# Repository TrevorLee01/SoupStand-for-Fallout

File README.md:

# Soup-Stand 🎧🦝 // FALLOUT PROJECT
A multifunctional pastel and tanuki (Soup!) themed headphone stand with integrated speaker, storage, and cable organization.

Created by Youna Son & Trevor Lee for Fallout / Hack Club.
✍️(◔◡◔)

ONSHAPE LINK: https://cad.onshape.com/documents/8000dcbb44917720ecbb4f72/w/cf3f842479549c0ffed44f74/e/c42a8c0b9d5092f488456cc3

  BOM INCLUDED IN THE FILES! "BOM.csv" 
or:
https://docs.google.com/spreadsheets/d/1DdpiUlOQK0JWII-2MIieYWEtMwIM88fONbokk5xA5AE/edit?gid=0#gid=0

______________

# What Is A Soup Stand ❓ο(=•ω＜=)ρ⌒☆
A Soup Stand is a hybrid desk accessory designed to combine organization, audio, and aesthetics into a single, cute tanuki.

The project combines:
- A headphone stand
- Speaker
- Compact desk organization
- Decorative accessory

The design was inspired by:
- pastel tech aesthetics (I've always wanted a cute set-up 💔)
- Japanese lifstyle product design (look how Muji designs their aesthetically pleasing stationary!)

+ gaming/anime desk culture:

But now... imagine the Soup Stand in these images

Unlike most headphone stads that are purely functional and even weirdly abstract looking, our product is designed to feel cozy. 

_________________

# Why It Was Made 🛠️ o(*￣▽￣*)o

We noticed that most desk accessories feel:
- boringggggggg
- overly industrial (late-stage capitalism tsk tsk)
- visually disconnected from modern aesthetic setups

At the same time, headphones are left:
- on desks (takes so much space on my limited desk space)
- hanging off monitors
- tangled in wires

So..
We wanted to create something that:
1) organizees a worspace
2) improves desk appearance
3) emotionally engaging rather than purely mechanical

A major goal of this project was combing hardware engineering (the opportunity fallout gives us) with product branding and visual interesting design

__________

# Features ✨   (*^▽^*)
## 🎧 Headphone Stand 
Supports over-ear headphones while keeping them accessible and off and desk surface 
## 🔊 Speaker
Internal space planned for small speaker 

~ plays your favorite song ~
## 🎨Decorative Design 

This structure is designed around 3D printing and prototyping!

________

# How It Works ╰(*°▽°*)╯

The headphones rest of the upper support section of the stand.

The lower body contains:
- eletronic compartment
- structural support (flat base)
- speakers

There are 3 buttons:
TOP: increase volume
MIDDLE: pause music/sound
BOTTOM: decrease volume

All 3 at once is the power on and off button

  !! POTENTIALLY:customizable parts ?? !!
  __________

  # How to build
  ______
  How to Assemble & Use Your Soup Stand
1) Print the Parts: Download the .step files from the repository and 3D print the upper headset support, main body, and base storage compartment.

2) Mount the Electronics: Secure your custom PCB inside the lower electronic compartment. Fit the speaker into its designated internal slot.

3) Route the Cables & Connect: Pass your speaker and power cables through the integrated cable organization channels out to the back of the stand.

4) Final Assembly: Align the upper support section with the main body and snap/screw them together.

5) How to Use: Place the Soup Stand on your desk and plug the power/audio cable into your computer or power source. Rest your over-ear headphones on Soup’s head to keep your desk clutter-free, use the lower tray for compact desk storage, and play your favorite music directly through the integrated speaker!

  # PICTURES!!!
  THIS OUR FINISHED CAD YAYYY (no color because we rendered it with color instead)

  THIS IS OUR PCB rah!!

  extra image of rendering not in the zine (NO FACE) :

# Credits
- Onshape (CAD)
- GitHub (here!)
- Canva (Zine)
- 3D printing
- and obviously... FALLOUT! since our headphone stand is based off the mascot Soup!

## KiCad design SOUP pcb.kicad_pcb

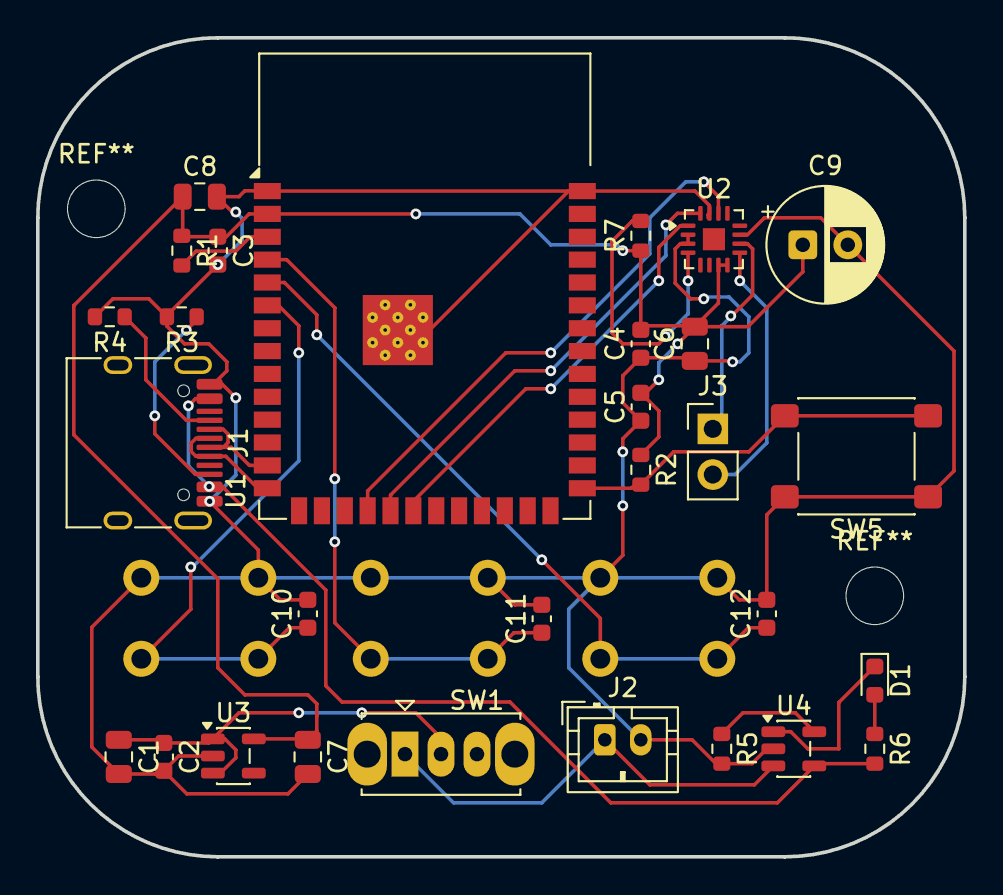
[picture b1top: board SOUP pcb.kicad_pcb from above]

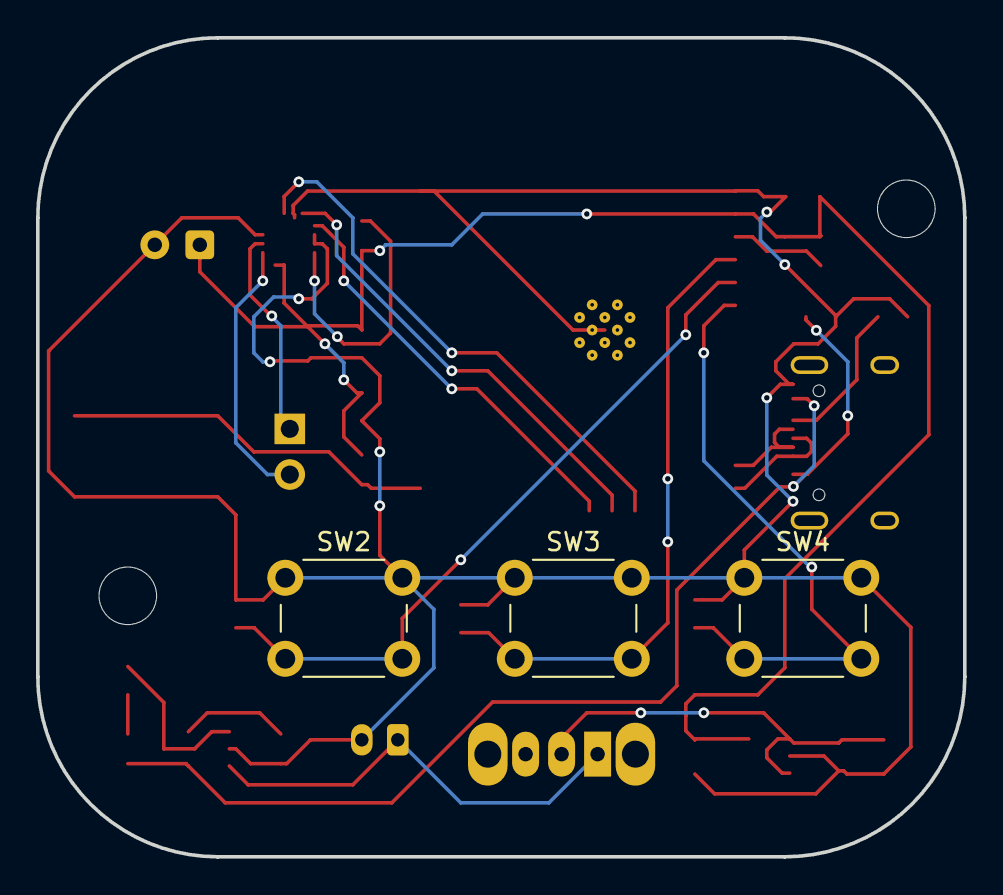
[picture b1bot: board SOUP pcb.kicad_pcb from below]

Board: 2 copper layers, 51.5 x 45.5 mm, 32 parts (3 on the bottom side), 23 nets.

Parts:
C1, C6, C7: 10μf; C_0805_2012Metric
C2, C4, C5, C10, C11, C12: 0.1μf; C_0603_1608Metric
C3: 1μf; C_0603_1608Metric
C8: 10 μf; C_0805_2012Metric
C9: 220μf; CP_Radial_D6.3mm_P2.50mm
D1: LED; LED_0603_1608Metric
J1: USB_C_Receptacle_USB2.0_16P; USB_C_Receptacle_HRO_TYPE-C-31-M-12
J2: Conn_01x02; JST_PH_B2B-PH-K_1x02_P2.00mm_Vertical
J3: Conn_01x02; PinHeader_1x02_P2.54mm_Vertical
R1: 10K; R_0603_1608Metric
R2: 10k; R_0603_1608Metric
R3, R4: 5.1K; R_0603_1608Metric
R5: 2k; R_0603_1608Metric
R6: 330; R_0603_1608Metric
R7: 300k; R_0603_1608Metric
SW1: SW_SPST; SW_Slide_SPDT_Straight_CK_OS102011MS2Q
SW2, SW3, SW4: SW_Push; SW_PUSH_6mm
SW5: SW_Push; SW_SPST_PTS645Sx43SMTR92
U1: ESP32-S3-WROOM-1
U2: MAX98357A; TQFN-16-1EP_3x3mm_P0.5mm_EP1.23x1.23mm
U3: AP2112K-3.3; SOT-23-5
U4: MCP73831-2-OT; SOT-23-5

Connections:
+3V3: C3.1, C4.2, C5.2, C6.2, C7.1, C8.1, C9.1, R1.1, R2.1, R7.1, U1.2 (3V3), U2.7 (VDD), U2.8 (VDD), U3.5 (VOUT)
/BTN_DOWN: C10.1, SW4.2, U1.6 (IO6)
/BTN_PLAY: C11.1, SW3.2, U1.4 (IO4)
/BTN_UP: C12.1, SW2.2, U1.5 (IO5)
/SPK+: J3.1, U2.10 (OUTN)
/SPK-: J3.2, U2.9 (OUTP)
/USBD+: J1.A6 (D+), J1.B6 (D+), U1.14 (USB_D+)
/USBD-: J1.A7 (D-), J1.B7 (D-), U1.13 (USB_D-)
/VBAT: J2.1, SW1.1 (A), U4.3 (V_{BAT})
GND: C1.2, C2.2, C3.2, C4.1, C5.1, C6.1, C7.2, C8.2, C9.2, C10.2, C11.2, C12.2, J1.A1 (GND), J1.A12 (GND), J1.B1 (GND), J1.B12 (GND), J2.2, R3.2, R4.2, R5.2, SW2.1, SW3.1, SW4.1, SW5.1, U1.1 (GND), U1.40 (GND), U1.41 (GND), U2.2 (GAIN_SLOT), U2.3 (GND), U2.11 (GND), U2.15 (GND), U3.2 (GND), U4.2 (V_{SS})
unnamed: D1.2 (A), R6.1
unnamed: D1.1 (K), U4.1 (STAT)
unnamed: J1.A5 (CC1), R4.1
unnamed: J1.B5 (CC2), R3.1
unnamed: C1.1, C2.1, SW1.2 (B), U3.1 (VIN), U3.3 (EN)
unnamed: R1.2, U1.3 (EN)
unnamed: R2.2, SW5.2, U1.27 (IO0)
unnamed: U1.18 (IO10), U2.14 (LRCLK)
unnamed: U1.19 (IO11), U2.16 (BCLK)
unnamed: U1.20 (IO12), U2.1 (DIN)
unnamed: R7.2, U2.4 (~SD_MODE)
unnamed: R5.1, U4.5 (PROG)
unnamed: J1.A4 (VBUS), J1.A9 (VBUS), J1.B4 (VBUS), J1.B9 (VBUS), R6.2, U4.4 (V_{DD})

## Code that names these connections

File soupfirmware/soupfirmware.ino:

#include <Arduino.h>
#include <WiFi.h>
#include "Audio.h"

//==================================================================
//firmware

//wifi placeholders (replace later with real wifi network)
#define WIFI_SSID "wifiname"
#define WIFI_PASSWORD "wifipassword"

//audio (placeholder)
#define AUDIO_STREAM_URL "streamurl"


//i25 pins from schematic
#define I2S_LRC 10
#define I2S_BCLK 11
#define I2S_DOUT 12

//button pins 
#define BTN_PLAY 4
#define BTN_UP 5
#define BTN_DOWN 6

//probably 0-21 in volunme right?
#define MIN_VOLUME 0
#define MAX_VOLUME 21
#define START_VOLUME 12

#define DEBOUNCE_MS 40

class DebouncedButton{
  private: 
    uint8_t pin;
    bool stableState;
    bool lastReading;
    unsigned long lastChangeTime;

  public:
    DebouncedButton(uint8_t buttonPin)
    : pin(buttonPin), stableState(HIGH), lastReading(HIGH), lastChangeTime(0) {

    }
    void begin(){
      pinMode(pin, INPUT_PULLUP);
      stableState = digitalRead(pin);
      lastReading = stableState;
    }

    bool wasPressed(){
        bool reading = digitalRead(pin);

        if(reading != lastReading){
          lastChangeTime = millis();
          lastReading = reading;
        }

        if((millis()- lastChangeTime) > DEBOUNCE_MS && reading!= stableState){
          stableState = reading;
        
          if(stableState == LOW){
            return true;
          }
        }
        return false;
    }
};

class HeadphoneStandPlayer{
  private:
    Audio audio;
    DebouncedButton playButton;
    DebouncedButton volumeUpButton;
    DebouncedButton volumeDownButton;

    int volume;
    bool streamStarted;
    bool streamPaused;

    public:
      HeadphoneStandPlayer()
      : playButton(BTN_PLAY), volumeUpButton(BTN_UP), volumeDownButton(BTN_DOWN),volume(START_VOLUME), streamStarted(false),
      streamPaused(false){}

      void begin(){
        playButton.begin();
        volumeUpButton.begin();
        volumeDownButton.begin();

        audio.setPinout(I2S_BCLK, I2S_LRC, I2S_DOUT);
        audio.setVolume(volume);

        Serial.println("Audio hardware ready ヽ(✿ﾟ▽ﾟ)ノ");
        Serial.println("Press PLAY to start the Wi-Fi stream o(*^＠^*)o");

      }

      void update(){
        audio.loop();
        if(playButton.wasPressed()){
          handlePlayButton();
        }

        if(volumeUpButton.wasPressed()){
          changeVolume(1);
        }

        if(volumeDownButton.wasPressed()){
          changeVolume(-1);
        }
      }
  private: 
    void handlePlayButton(){
      if(!streamStarted){
        Serial.println("PLAY pressed: starting stream (☞ﾟヮﾟ)☞ ☜(ﾟヮﾟ☜)");
        audio.connecttohost(AUDIO_STREAM_URL);
        streamStarted = true;
        streamPaused = false;
        return;
      }

      audio.pauseResume();
      streamPaused = !streamPaused;
    }
    void changeVolume(int amount){
      volume+= amount;

      if(volume<MIN_VOLUME){
        volume = MIN_VOLUME;
      }

      if(volume>MAX_VOLUME){
        volume = MAX_VOLUME;
      }

      audio.setVolume(volume);
      Serial.print("Volume: ");
      Serial.println(volume);
    }
};

HeadphoneStandPlayer player;

void connectToWifi(){
  Serial.print("Connecting to Wi-Fi o(￣▽￣)ｄ");

  WiFi.mode(WIFI_STA);
  WiFi.begin(WIFI_SSID, WIFI_PASSWORD);

  while(WiFi.status() != WL_CONNECTED){
    delay(250);
    Serial.print(".");
  }

  Serial.println();
  Serial.println("Wi-Fi connected.");
  Serial.print("IP address: ");
  Serial.println(WiFi.localIP());
}

void setup(){
  Serial.begin(115200);
  delay(500);

  connectToWifi();
  player.begin();
}

void loop(){
  player.update();
}

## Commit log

2026-05-24 Revise README for Soup-Stand project details
    Updated project description and added details about features, design inspiration, and development progress.
2026-05-25 Revise README with emojis and section enhancements
    Updated README.md with new emojis and improved phrasing for sections.
2026-06-12 Rename peenar.kicad_sch to soup.kicad_sch
2026-06-14 Clean up README by removing extra information
    Removed unnecessary sections and updated formatting.
2026-06-20 Create pcb
2026-06-20 Create stuff
2026-06-20 Rename SOUP pcb (1).kicad_sch to SOUP pcb.kicad_sch
2026-06-20 Rename Soup - Sheet1.csv to BOM.csv
2026-06-20 Rename Soup - Sheet1 (1).csv to bom.csv
2026-06-21 Rename Soup Stand (1).png to SoupStandZine.png
2026-06-21 renaming files
2026-06-21 Revise README with features and assembly details
    Updated README to include additional features, assembly instructions, and images for the Soup Stand project.
2026-06-21 format issues
    Updated the README to enhance project description and features.
2026-06-23 Rename bom.csv to BOM.csv
